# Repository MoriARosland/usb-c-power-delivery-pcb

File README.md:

# usb-c-power-delivery-pcb

100W power supply through USB-C PD Revision 3.1

_(Design complete, but revision in progress)_

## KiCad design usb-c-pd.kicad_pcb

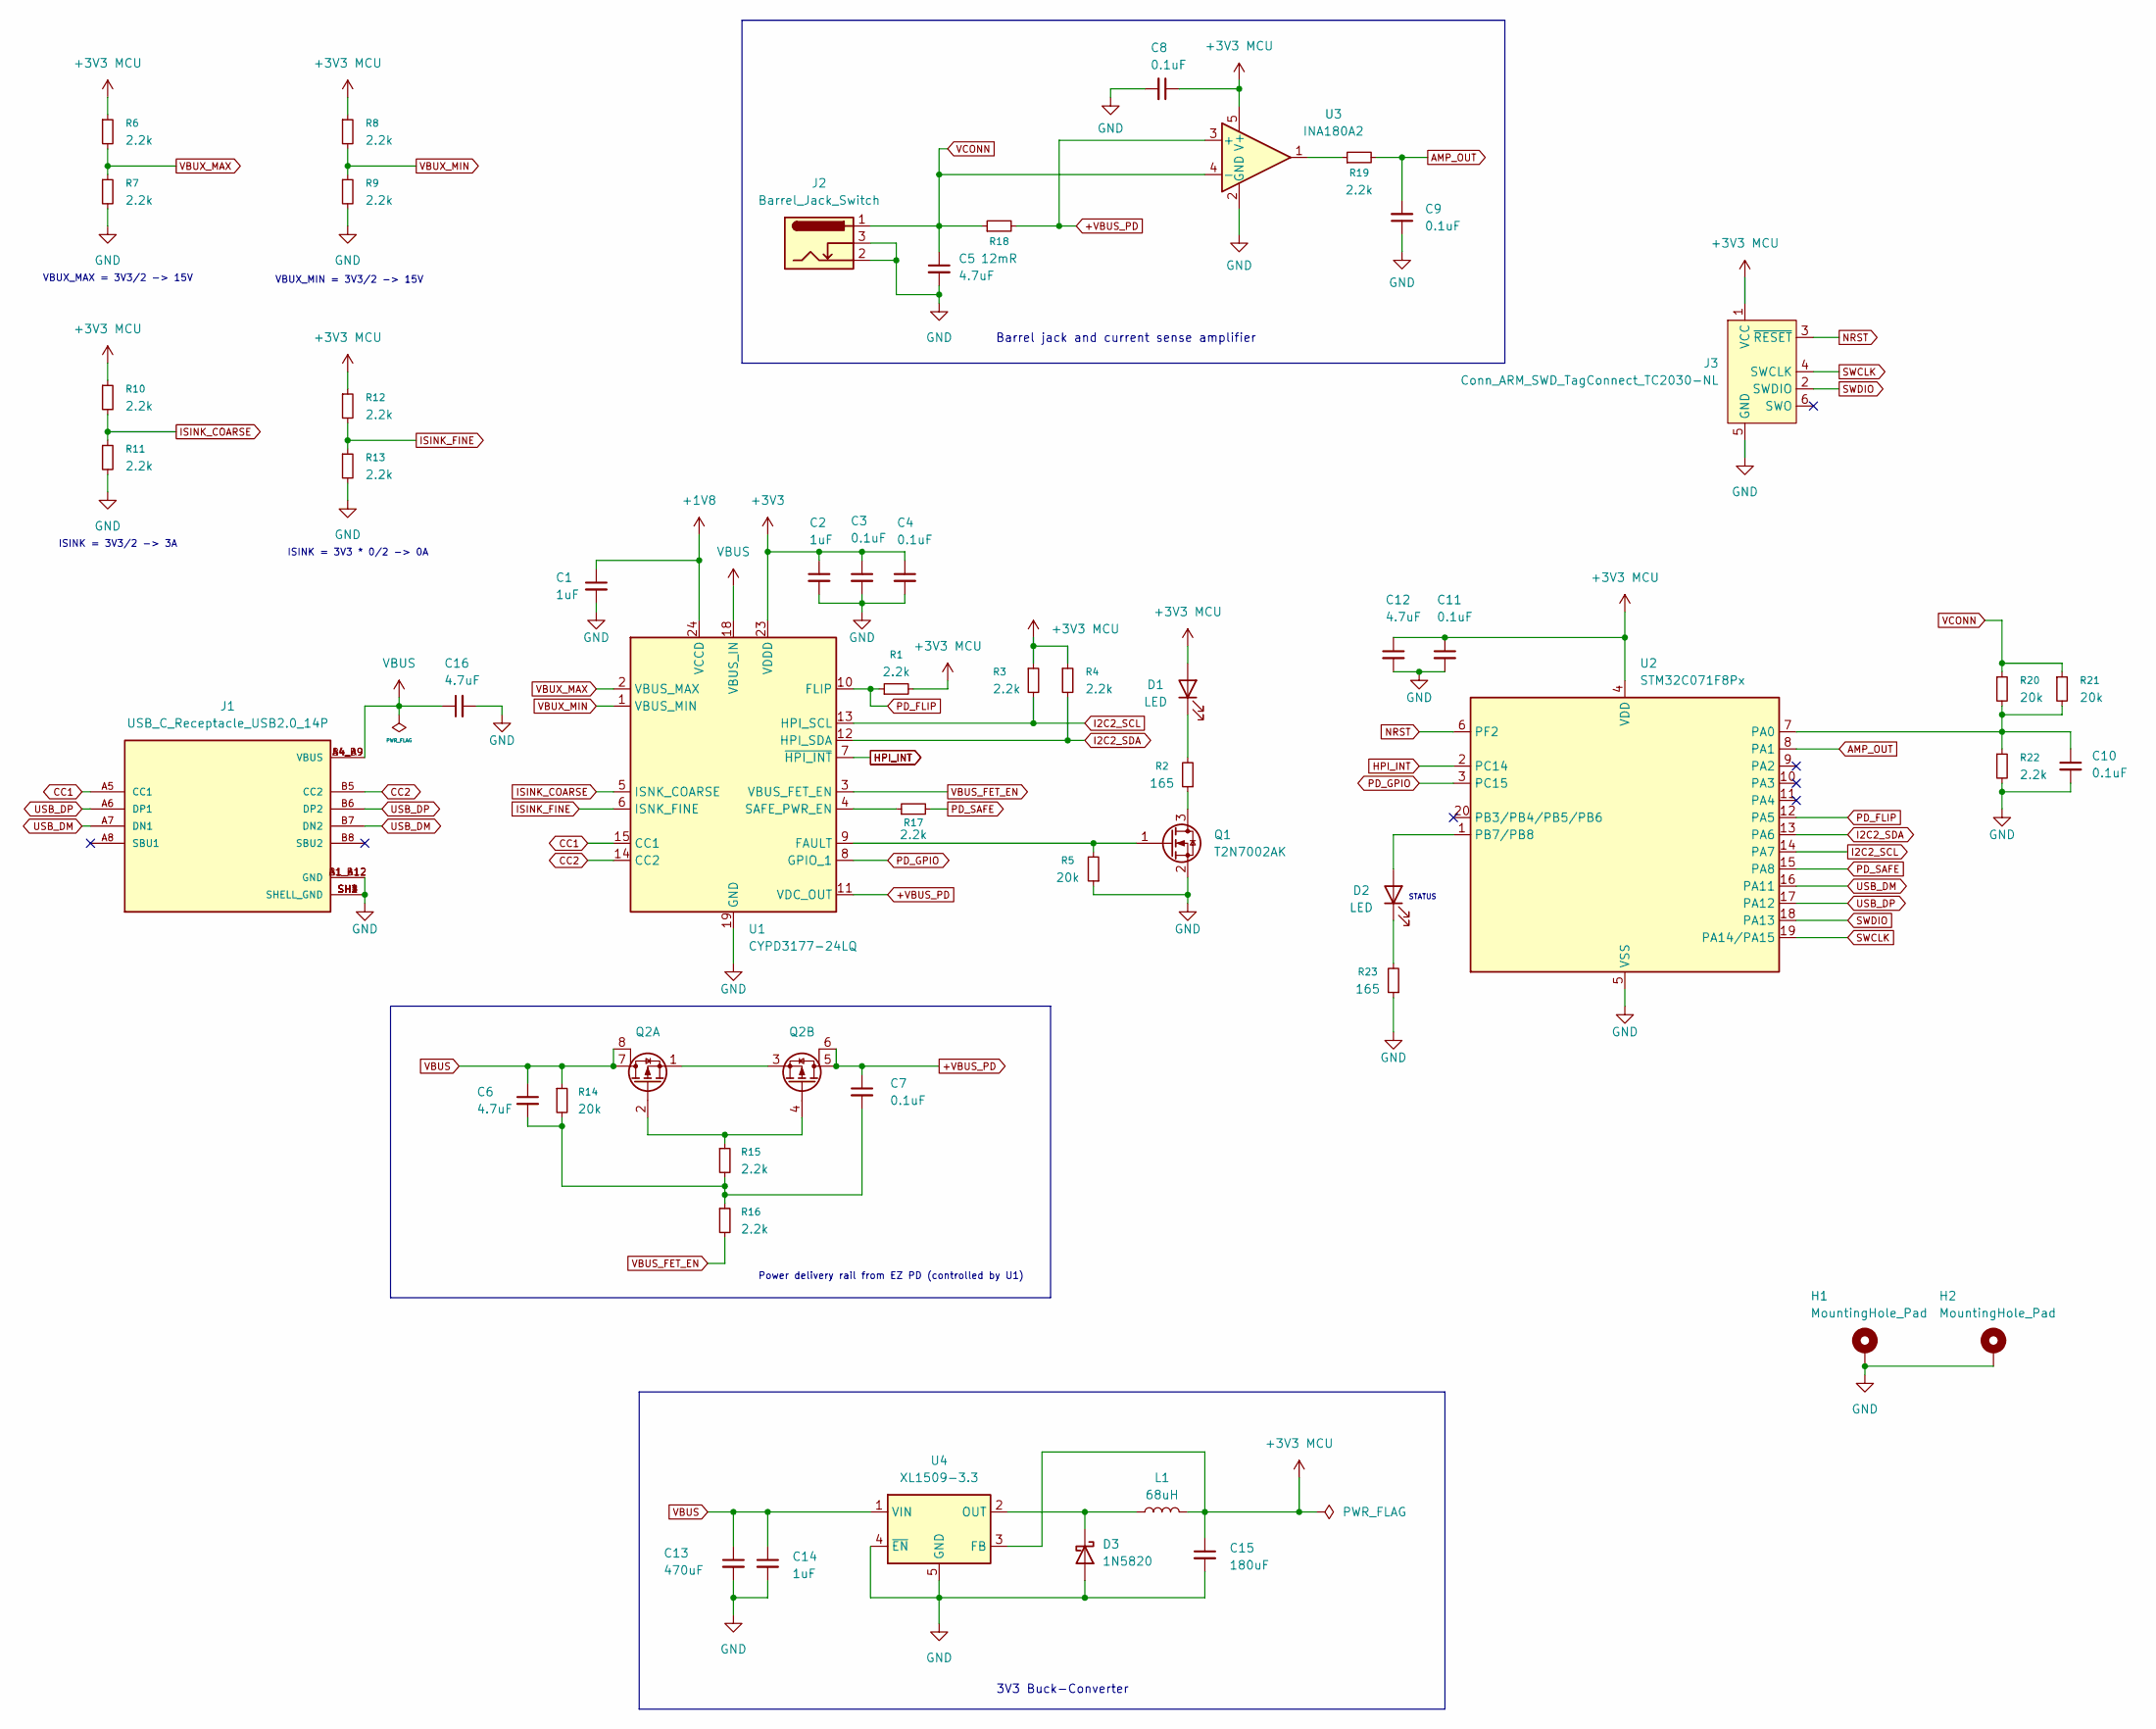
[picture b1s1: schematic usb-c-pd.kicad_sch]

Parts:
C1, C2, C14: 1uF; C_0603_1608Metric_Pad1.08x0.95mm_HandSolder
C3, C4, C7, C8, C9, C10, C11: 0.1uF; C_0603_1608Metric_Pad1.08x0.95mm_HandSolder
C5, C6, C12, C16: 4.7uF; C_0603_1608Metric_Pad1.08x0.95mm_HandSolder
C13: 470uF; C_0603_1608Metric_Pad1.08x0.95mm_HandSolder
C15: 180uF; C_0603_1608Metric_Pad1.08x0.95mm_HandSolder
D1, D2: LED; D_0603_1608Metric_Pad1.05x0.95mm_HandSolder
D3: 1N5820; D_0603_1608Metric_Pad1.05x0.95mm_HandSolder
H1, H2: MountingHole_Pad; MountingHole_3.2mm_M3_DIN965_Pad
J1: USB_C_Receptacle_USB2.0_14P; GCT_USB4105-GF-A; PARTREV B4; DigiKey_Part_Number 2073-USB4105-GF-ACT-ND
J2: Barrel_Jack_Switch; PJ002AHSMTTR
J3: Conn_ARM_SWD_TagConnect_TC2030-NL; Tag-Connect_TC2030-IDC-NL_2x03_P1.27mm_Vertical
L1: 68uH; L_0603_1608Metric_Pad1.05x0.95mm_HandSolder
Q1: T2N7002AK; SOT-23
Q2: SOIC127P600X175-8N
R1, R3, R4, R6, R7, R8, R9, R10, R11, R12, R13, R15, R16, R17, R19, R22: 2.2k; R_0603_1608Metric_Pad0.98x0.95mm_HandSolder
R2, R23: 165; R_0603_1608Metric_Pad0.98x0.95mm_HandSolder
R5, R14, R20, R21: 20k; R_0603_1608Metric_Pad0.98x0.95mm_HandSolder
R18: 12mR; R_0603_1608Metric_Pad0.98x0.95mm_HandSolder
U1: CYPD3177-24LQ; QFN-24-1EP_4x4mm_P0.5mm_EP2.75x2.75mm
U2: STM32C071F8Px; TSSOP-20_4.4x6.5mm_P0.65mm
U3: INA180A2; SOT-23-5
U4: XL1509-3.3; SOIC-8_3.9x4.9mm_P1.27mm

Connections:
+1V8: C1.1, U1.24 (VCCD)
+3V3: C2.1, C3.1, C4.1, U1.23 (VDDD)
+3V3 MCU: C8.1, C11.1, C12.1, C15.1, D1.2 (A), J3.1 (VCC), L1.2, R1.2, R3.1, R4.1, R6.1, R8.1, R10.1, R12.1, U2.4 (VDD), U3.5 (V+), U4.3 (FB)
+VBUS_PD: C7.1, Q2.5 (D2), Q2.6 (D2), R18.2, U1.11 (VDC_OUT), U3.3 (+)
AMP_OUT: C9.2, R19.2, U2.8 (PA1)
CC1: J1.A5 (CC1), U1.15 (CC1)
CC2: J1.B5 (CC2), U1.14 (CC2)
GND: C1.2, C2.2, C3.2, C4.2, C5.2, C8.2, C9.1, C10.2, C11.2, C12.2, C13.2, C14.2, C15.2, C16.2, D3.2 (A), H1.1, H2.1, J1.A1_B12 (GND), J1.B1_A12 (GND), J1.SH1 (SHELL_GND), J1.SH2 (SHELL_GND), J1.SH3 (SHELL_GND), J1.SH4 (SHELL_GND), J2.2, J2.3, J3.5 (GND), Q1.2 (S), R5.1, R7.2, R9.2, R11.2, R13.2, R22.2, R23.1, U1.19 (GND), U1.22 (GND), U1.25 (GND), U2.5 (VSS), U3.2 (GND), U4.4 (~EN), U4.5 (GND), U4.6 (GND), U4.7 (GND), U4.8 (GND)
HPI_INT: U1.7 (~HPI_INT), U2.2 (PC14)
I2C2_SCL: R3.2, U1.13 (HPI_SCL), U2.14 (PA7)
I2C2_SDA: R4.2, U1.12 (HPI_SDA), U2.13 (PA6)
ISINK_COARSE: R10.2, R11.1, U1.5 (ISNK_COARSE)
ISINK_FINE: R12.2, R13.1, U1.6 (ISNK_FINE)
NRST: J3.3 (~RESET), U2.6 (PF2)
unnamed: C6.2, C7.2, R14.2, R15.2, R16.1
unnamed: D1.1 (K), R2.2
unnamed: D2.2 (A), U2.1 (PB7/PB8)
unnamed: D2.1 (K), R23.2
unnamed: D3.1 (K), L1.1, U4.2 (OUT)
unnamed: Q1.3 (D), R2.1
unnamed: Q1.1 (G), R5.2, U1.9 (FAULT)
unnamed: Q2.2 (G1), Q2.4 (G2), R15.1
unnamed: Q2.1 (S1), Q2.3 (S2)
unnamed: R19.1, U3.1
unnamed: R17.1, U1.4 (SAFE_PWR_EN)
unnamed: C10.1, R20.2, R21.2, R22.1, U2.7 (PA0)
PD_FLIP: R1.1, U1.10 (FLIP), U2.12 (PA5)
PD_GPIO: U1.8 (GPIO_1), U2.3 (PC15)
PD_SAFE: R17.2, U2.15 (PA8)
SWCLK: J3.4 (SWCLK), U2.19 (PA14/PA15)
SWDIO: J3.2 (SWDIO), U2.18 (PA13)
USB_DM: J1.A7 (DN1), J1.B7 (DN2), U2.16 (PA11)
USB_DP: J1.A6 (DP1), J1.B6 (DP2), U2.17 (PA12)
VBUS: C6.1, C13.1, C14.1, C16.1, J1.A4_B9 (VBUS), J1.B4_A9 (VBUS), Q2.7 (D), Q2.8 (D), R14.1, U1.18 (VBUS_IN), U4.1 (VIN)
VBUS_FET_EN: R16.2, U1.3 (VBUS_FET_EN)
VBUX_MAX: R6.2, R7.1, U1.2 (VBUS_MAX)
VBUX_MIN: R8.2, R9.1, U1.1 (VBUS_MIN)
VCONN: C5.1, J2.1, J2.A1, R18.1, R20.1, R21.1, U3.4 (-)

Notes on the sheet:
3V3 Buck-Converter
Power delivery rail from EZ PD (controlled by U1)
STATUS
Barrel jack and current sense amplifier
VBUX_MAX = 3V3/2 -> 15V
VBUX_MIN = 3V3/2 -> 15V
ISINK = 3V3 * 0/2 -> 0A
ISINK = 3V3/2 -> 3A

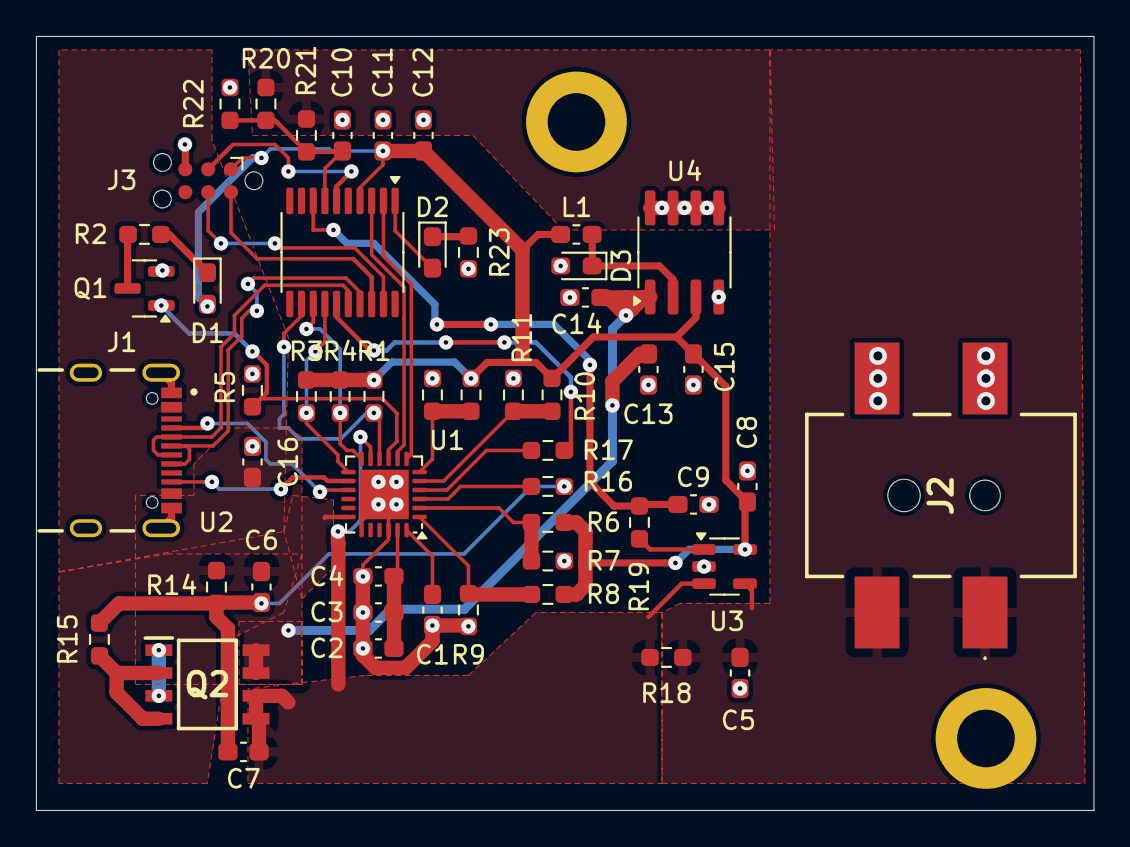
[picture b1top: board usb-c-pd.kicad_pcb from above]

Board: 2 copper layers, 58.8 x 43.0 mm, 54 parts (0 on the bottom side), 38 nets.

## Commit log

2025-07-16 configure project
2025-07-20 feat: add primary components
2025-07-26 feat: ez-pd
2025-08-02 feat: stm mcu
2025-08-02 feat: SWO programming
2025-08-09 verify ERC
2025-08-09 feat: mcu (#1)
    * feat: stm mcu
    * feat: SWO programming
    * verify ERC
2025-08-10 feat: configure footprints
2025-08-10 feat: configure footprints (#2)
    * feat: stm mcu
    * feat: SWO programming
    * verify ERC
    * feat: configure footprints
2025-08-10 feat: preliminary layout
2025-08-11 feat: routing
2025-08-11 feat: add 3d models and diode R values
2025-08-11 feat layout and routing (#3)
    * feat: preliminary layout
    * feat: routing
    * feat: add 3d models and diode R values
2025-08-12 feat: finalize design
2025-08-12 feat: finalize design (#4)
2025-08-12 feat: finalize design (#5)
2025-09-04 Add revision note to README
2025-09-04 Update README with project status clarification
2025-09-04 Update README with project details and status
